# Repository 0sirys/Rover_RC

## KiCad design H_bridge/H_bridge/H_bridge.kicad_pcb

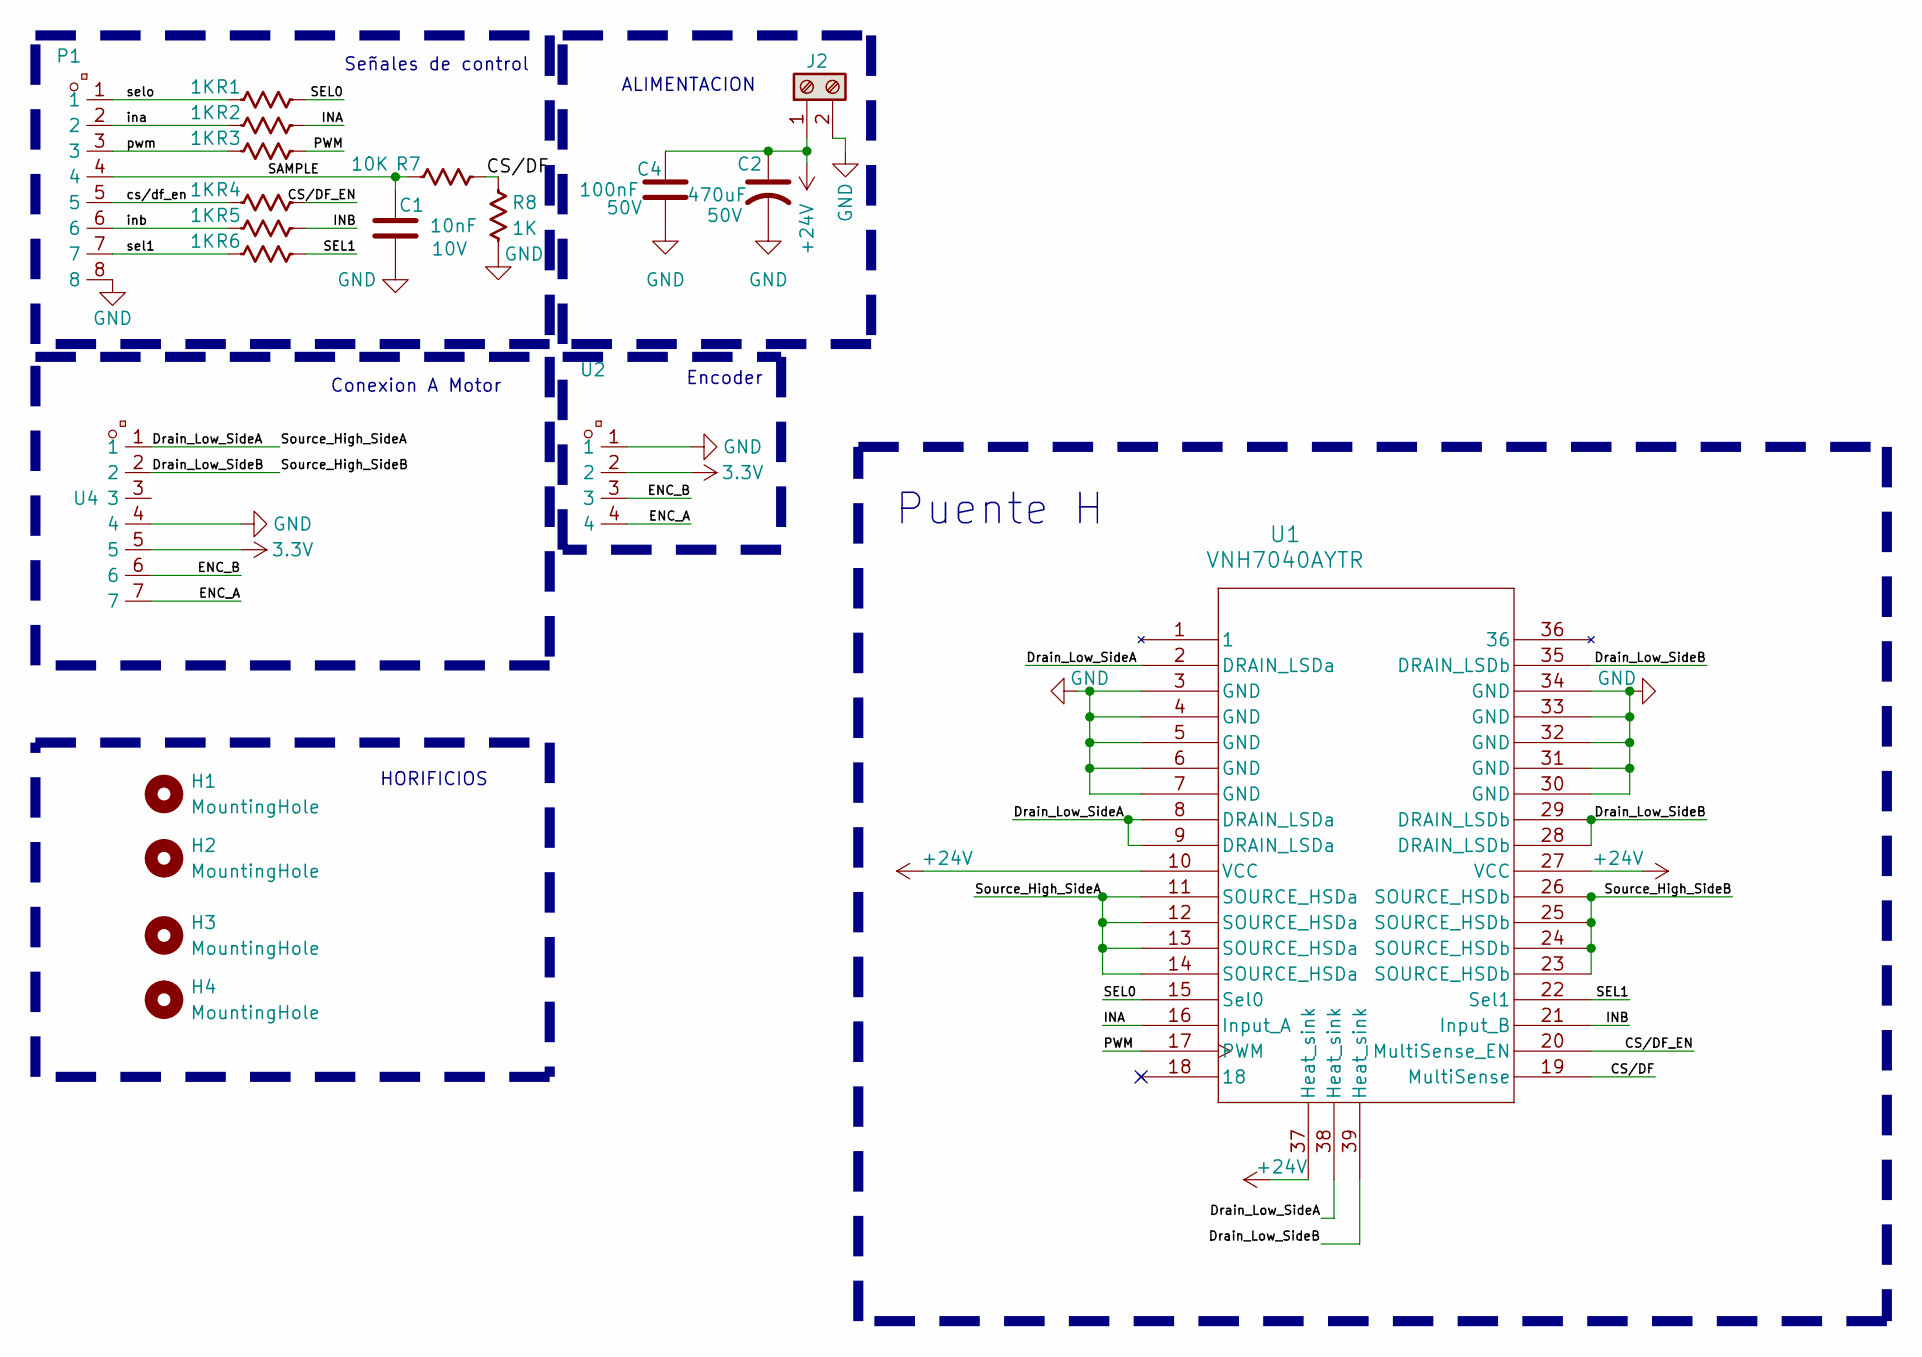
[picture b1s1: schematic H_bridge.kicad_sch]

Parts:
C1: 10nF; C_0603_1608Metric
C2: 470uF; CP_Elec_10x14.3
C4: 100nF; C_0805_2012Metric
H1, H2, H3, H4: MountingHole; MountingHole_2.2mm_M2
J2: Screw_Terminal_01x02; TerminalBlock_4Ucon_1x02_P3.50mm_Horizontal
P1: Header-Female-2.54_1x8; HDR-TH_8P-P2.54-V-F_2; LCSC Part C27438
R1, R2, R3, R4, R5, R6, R8: 1K; R_0603_1608Metric
R7: 10K; R_0603_1608Metric
U1: VNH7040AYTR; POWERSSO-36TP_STM-M
U2: HX PZ2.54-1X4P ZZ; HDR-TH_4P-P2.54-V-M; LCSC Part C32713270
U4: DB125-3.5-7P-GN-S; CONN-TH_7P-P3.50_DORABO_DB125-3.5-7P-GN-S; LCSC Part C5155542

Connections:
3.3V: U2.2, U4.5
+24V: C2.1, C4.1, J2.1, U1.10 (VCC), U1.27 (VCC), U1.37 (Heat_sink)
/CS/DF: R7.2, R8.2, U1.19 (MultiSense)
/CS/DF_EN: R4.2, U1.20 (MultiSense_EN)
/Drain_Low_SideA: U1.2 (DRAIN_LSDa), U1.8 (DRAIN_LSDa), U1.9 (DRAIN_LSDa), U1.11 (SOURCE_HSDa), U1.12 (SOURCE_HSDa), U1.13 (SOURCE_HSDa), U1.14 (SOURCE_HSDa), U1.38 (Heat_sink), U4.1
/Drain_Low_SideB: U1.23 (SOURCE_HSDb), U1.24 (SOURCE_HSDb), U1.25 (SOURCE_HSDb), U1.26 (SOURCE_HSDb), U1.28 (DRAIN_LSDb), U1.29 (DRAIN_LSDb), U1.35 (DRAIN_LSDb), U1.39 (Heat_sink), U4.2
/ENC_A: U2.4, U4.7
/ENC_B: U2.3, U4.6
/INA: R2.2, U1.16 (Input_A)
/INB: R5.2, U1.21 (Input_B)
/PWM: R3.2, U1.17 (PWM)
/SAMPLE: C1.1, P1.4, R7.1
/SEL0: R1.2, U1.15 (Sel0)
/SEL1: R6.2, U1.22 (Sel1)
/cs/df_en: P1.5, R4.1
/ina: P1.2, R2.1
/inb: P1.6, R5.1
/pwm: P1.3, R3.1
/sel1: P1.7, R6.1
/selo: P1.1, R1.1
GND: C1.2, C2.2, C4.2, J2.2, P1.8, R8.1, U1.3 (GND), U1.4 (GND), U1.5 (GND), U1.6 (GND), U1.7 (GND), U1.30 (GND), U1.31 (GND), U1.32 (GND), U1.33 (GND), U1.34 (GND), U2.1, U4.4

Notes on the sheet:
Encoder
Conexion A Motor
Señales de control
ALIMENTACION
HORIFICIOS
Puente H

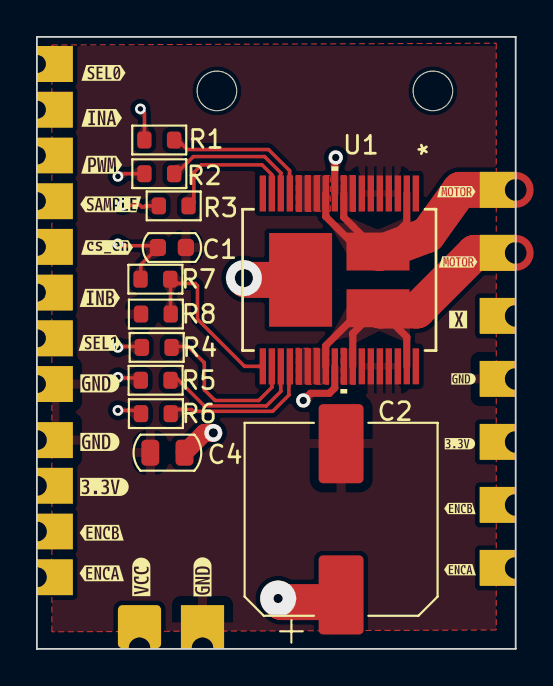
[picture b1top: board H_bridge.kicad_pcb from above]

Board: 4 copper layers, 26.6 x 34.0 mm, 41 parts (1 on the bottom side), 21 nets.

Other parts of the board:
kibuzzard-6918ABEE, kibuzzard-6918ABEE#2, kibuzzard-6918ABEE#3: G***; kibuzzard-6918ABEE
kibuzzard-6918ABFE: G***; kibuzzard-6918ABFE
kibuzzard-6918AEC8: G***; kibuzzard-6918AEC8
kibuzzard-6918AF5D: G***; kibuzzard-6918AF5D
kibuzzard-6918AF9A: G***; kibuzzard-6918AF9A
kibuzzard-6918AF91: G***; kibuzzard-6918AF91
kibuzzard-6918AFA7: G***; kibuzzard-6918AFA7
kibuzzard-6918AFBB: G***; kibuzzard-6918AFBB
kibuzzard-6918AFD3: G***; kibuzzard-6918AFD3
kibuzzard-6918B0DE: G***; kibuzzard-6918B0DE
kibuzzard-6918B0E8: G***; kibuzzard-6918B0E8
kibuzzard-6918B0F5: G***; kibuzzard-6918B0F5
kibuzzard-6918B09A: G***; kibuzzard-6918B09A
kibuzzard-6918BF9B, kibuzzard-6918BF9B#2: G***; kibuzzard-6918BF9B
kibuzzard-6918BFE8: G***; kibuzzard-6918BFE8
kibuzzard-6918C0A7: G***; kibuzzard-6918C0A7
kibuzzard-6918C0B5: G***; kibuzzard-6918C0B5
kibuzzard-6918C0C9: G***; kibuzzard-6918C0C9

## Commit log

2025-11-08 Primer Commit
2025-11-14 puente H, Done
2025-11-14 avances pcb
2025-11-15 instalacion de gui_impart
2025-11-15 Puente H Done
2025-11-15 ajuste capa
2025-11-15 salidas motor castellated
2025-11-18 version con filtro de ferrita y pinheaders
2025-11-19 Carpetas parasito borradas
2025-11-19 Cleaned main
2025-11-19 MCU datasheet
